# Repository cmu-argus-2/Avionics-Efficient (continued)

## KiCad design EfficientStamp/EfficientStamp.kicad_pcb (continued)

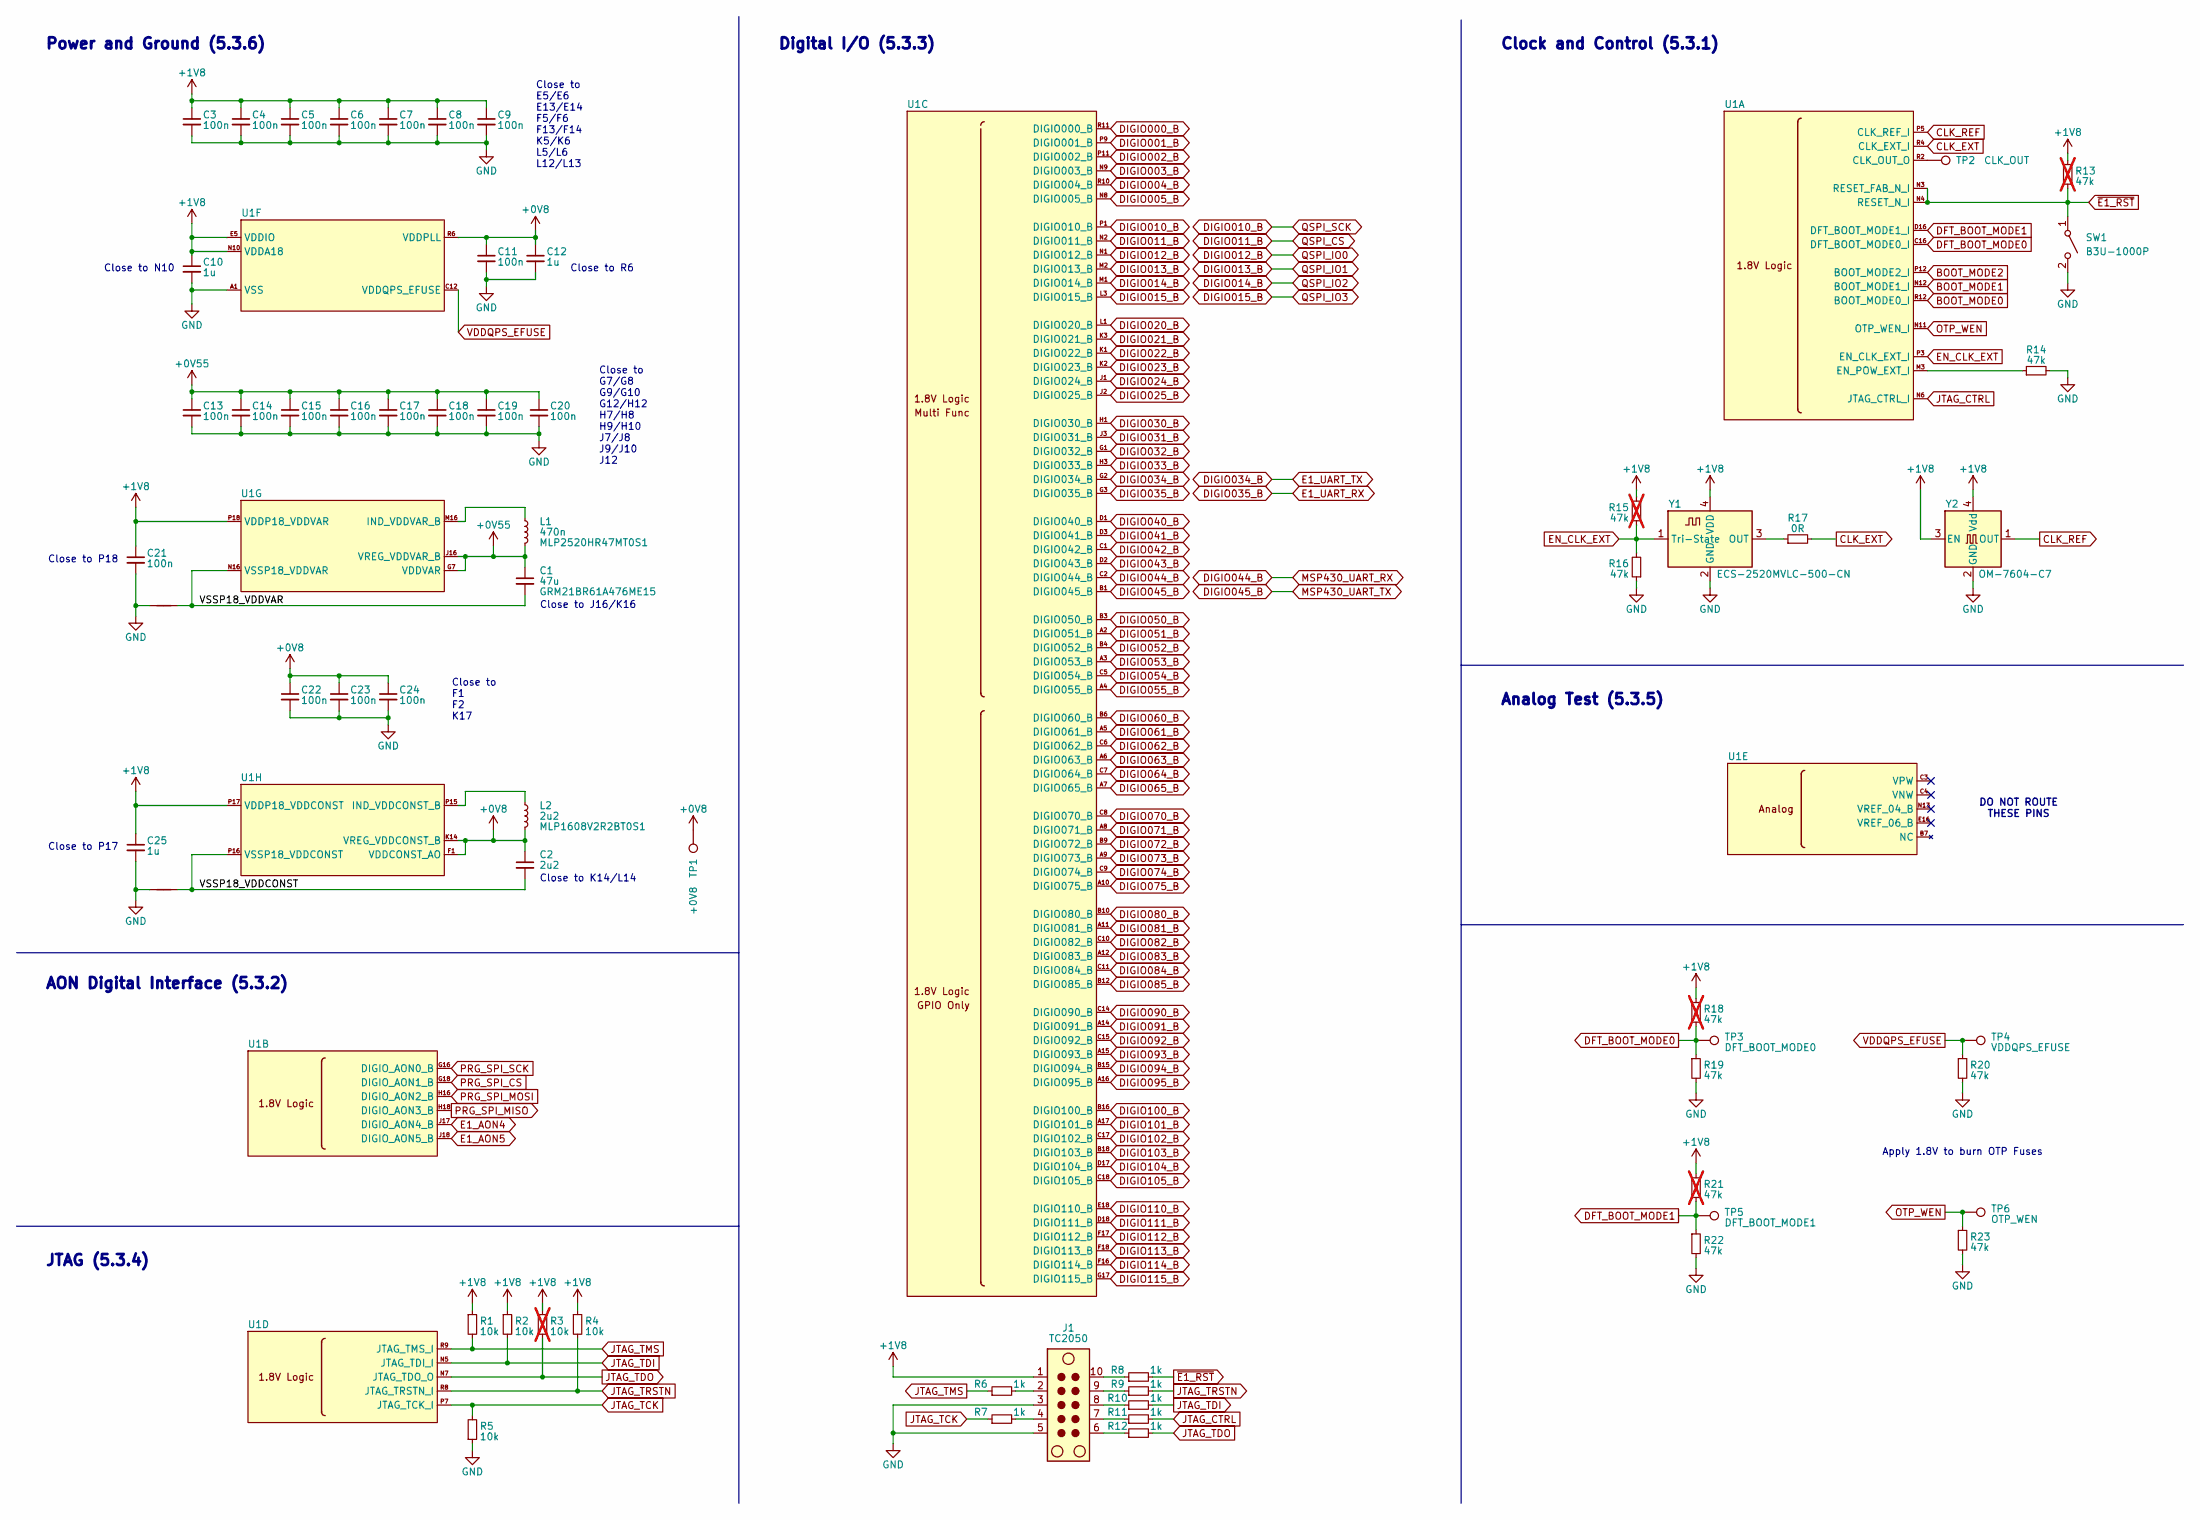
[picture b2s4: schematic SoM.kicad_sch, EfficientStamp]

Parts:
C1: 47u; C_0805_2012Metric; Part No. GRM21BR61A476ME15
C2: 2u2; C_0603_1608Metric
C3, C4, C5, C6, C7, C8, C9, C11, C13, C14, C15, C16, C17, C18, C19, C20, C21, C22, C23, C24: 100n; C_0201_0603Metric
C10, C12, C25: 1u; C_0402_1005Metric
J1: TC2050; Tag-Connect_TC2050-IDC-NL_2x05_P1.27mm_Vertical
L1: 470n; L_1008_2520Metric; Part No. MLP2520HR47MT0S1
L2: 2u2; L_0603_1608Metric; Part No. MLP1608V2R2BT0S1
NT1, NT2: NetTie_2; NetTie-2_SMD_Pad0.1mm
R1, R2, R4, R5: 10k; R_0402_1005Metric
R3: 10k; R_0402_1005Metric; not fitted
R6, R7, R8, R9, R10, R11, R12: 1k; R_0402_1005Metric
R13, R15, R18, R21: 47k; R_0402_1005Metric; not fitted
R14, R16, R19, R20, R22, R23: 47k; R_0402_1005Metric
R17: 0R; R_0402_1005Metric
SW1: B3U-1000P; SW_SPST_B3U-1000P
TP1: +0V8; TestPoint_Pad_D1.0mm
TP2: CLK_OUT; TestPoint_Pad_D1.0mm
TP3: DFT_BOOT_MODE0; TestPoint_Pad_D1.0mm
TP4: VDDQPS_EFUSE; TestPoint_Pad_D1.0mm
TP5: DFT_BOOT_MODE1; TestPoint_Pad_D1.0mm
TP6: OTP_WEN; TestPoint_Pad_D1.0mm
U1: Efficient E1x; WB-BGA-219_8.3x7.1mm_Layout17x15_P0.45mm_Ball0.45mm_Pad0.32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
Y1: ECS-2520MVLC-500-CN; Oscillator_SMD_ECS_2520MV-xxx-xx-4Pin_2.5x2.0mm
Y2: OM-7604-C7; OSC_OM-7604-C7-32.768KHZ-20PPM-TA-QC

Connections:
+0V8: C2.1, C11.1, C12.1, C22.1, C23.1, C24.1, L2.2, TP1.1 (1_1), U1.F1 (VDDCONST_AO), U1.F2 (VDDCONST_AO), U1.F3 (VDDCONST_AO), U1.K14 (VREG_VDDCONST_B), U1.K17 (VDDCONST_AO), U1.K18 (VDDCONST_AO), U1.L14 (VREG_VDDCONST_B), U1.R6 (VDDPLL)
+0V55: C1.1, C13.1, C14.1, C15.1, C16.1, C17.1, C18.1, C19.1, C20.1, L1.2, U1.G7 (VDDVAR), U1.G8 (VDDVAR), U1.G9 (VDDVAR), U1.G10 (VDDVAR), U1.G12 (VDDVAR), U1.H7 (VDDVAR), U1.H8 (VDDVAR), U1.H9 (VDDVAR), U1.H10 (VDDVAR), U1.H12 (VDDVAR), U1.J7 (VDDVAR), U1.J8 (VDDVAR), U1.J9 (VDDVAR), U1.J10 (VDDVAR), U1.J12 (VDDVAR), U1.J16 (VREG_VDDVAR_B), U1.K16 (VREG_VDDVAR_B); also elsewhere on the board
+1V8: C3.1, C4.1, C5.1, C6.1, C7.1, C8.1, C9.1, C10.1, C21.1, C25.1, J1.1, R1.1, R2.1, R3.1, R4.1, R13.2, R15.2, R18.1, R21.1, U1.E5 (VDDIO), U1.E6 (VDDIO), U1.E13 (VDDIO), U1.E14 (VDDIO), U1.F5 (VDDIO), U1.F6 (VDDIO), U1.F13 (VDDIO), U1.F14 (VDDIO), U1.K5 (VDDIO), U1.K6 (VDDIO), U1.L5 (VDDIO), U1.L6 (VDDIO), U1.L12 (VDDIO), U1.L13 (VDDIO), U1.N10 (VDDA18), U1.P17 (VDDP18_VDDCONST), U1.P18 (VDDP18_VDDVAR), U1.R17 (VDDP18_VDDCONST), U1.R18 (VDDP18_VDDVAR), Y1.4 (VDD), Y2.3 (EN), Y2.4 (Vdd); also elsewhere on the board
BOOT_MODE0: U1.R12 (BOOT_MODE0_I); also elsewhere on the board
BOOT_MODE1: U1.N12 (BOOT_MODE1_I); also elsewhere on the board
BOOT_MODE2: U1.P12 (BOOT_MODE2_I); also elsewhere on the board
CLK_EXT: R17.2, U1.R4 (CLK_EXT_I)
CLK_REF: U1.P5 (CLK_REF_I), Y2.1 (OUT)
DFT_BOOT_MODE0: R18.2, R19.1, TP3.1 (1_1), U1.C16 (DFT_BOOT_MODE0_I)
DFT_BOOT_MODE1: R21.2, R22.1, TP5.1 (1_1), U1.D16 (DFT_BOOT_MODE1_I)
DIGIO000_B: U1.R11 (DIGIO000_B); also elsewhere on the board
DIGIO001_B: U1.P9 (DIGIO001_B); also elsewhere on the board
DIGIO002_B: U1.P11 (DIGIO002_B); also elsewhere on the board
DIGIO003_B: U1.N9 (DIGIO003_B); also elsewhere on the board
DIGIO004_B: U1.R10 (DIGIO004_B); also elsewhere on the board
DIGIO005_B: U1.N8 (DIGIO005_B); also elsewhere on the board
DIGIO010_B: U1.P1 (DIGIO010_B); also elsewhere on the board
DIGIO011_B: U1.N2 (DIGIO011_B); also elsewhere on the board
DIGIO012_B: U1.N1 (DIGIO012_B); also elsewhere on the board
DIGIO013_B: U1.M2 (DIGIO013_B); also elsewhere on the board
DIGIO014_B: U1.M1 (DIGIO014_B); also elsewhere on the board
DIGIO015_B: U1.L3 (DIGIO015_B); also elsewhere on the board
DIGIO020_B: U1.L1 (DIGIO020_B); also elsewhere on the board
DIGIO021_B: U1.K3 (DIGIO021_B); also elsewhere on the board
DIGIO022_B: U1.K1 (DIGIO022_B); also elsewhere on the board
DIGIO023_B: U1.K2 (DIGIO023_B); also elsewhere on the board
DIGIO024_B: U1.J1 (DIGIO024_B); also elsewhere on the board
DIGIO025_B: U1.J2 (DIGIO025_B); also elsewhere on the board
DIGIO030_B: U1.H1 (DIGIO030_B); also elsewhere on the board
DIGIO031_B: U1.J3 (DIGIO031_B); also elsewhere on the board
DIGIO032_B: U1.G1 (DIGIO032_B); also elsewhere on the board
DIGIO033_B: U1.H3 (DIGIO033_B); also elsewhere on the board
DIGIO034_B: U1.G2 (DIGIO034_B); also elsewhere on the board
DIGIO035_B: U1.G3 (DIGIO035_B); also elsewhere on the board
DIGIO040_B: U1.D1 (DIGIO040_B); also elsewhere on the board
DIGIO041_B: U1.D3 (DIGIO041_B); also elsewhere on the board
DIGIO042_B: U1.C1 (DIGIO042_B); also elsewhere on the board
DIGIO043_B: U1.D2 (DIGIO043_B); also elsewhere on the board
DIGIO044_B: U1.C2 (DIGIO044_B); also elsewhere on the board
DIGIO045_B: U1.B1 (DIGIO045_B); also elsewhere on the board
DIGIO050_B: U1.B3 (DIGIO050_B); also elsewhere on the board
DIGIO051_B: U1.A2 (DIGIO051_B); also elsewhere on the board
DIGIO052_B: U1.B4 (DIGIO052_B); also elsewhere on the board
DIGIO053_B: U1.A3 (DIGIO053_B); also elsewhere on the board
DIGIO054_B: U1.C5 (DIGIO054_B); also elsewhere on the board
DIGIO055_B: U1.A4 (DIGIO055_B); also elsewhere on the board
DIGIO060_B: U1.B6 (DIGIO060_B); also elsewhere on the board
DIGIO061_B: U1.A5 (DIGIO061_B); also elsewhere on the board
DIGIO062_B: U1.C6 (DIGIO062_B); also elsewhere on the board
DIGIO063_B: U1.A6 (DIGIO063_B); also elsewhere on the board
DIGIO064_B: U1.C7 (DIGIO064_B); also elsewhere on the board
DIGIO065_B: U1.A7 (DIGIO065_B); also elsewhere on the board
DIGIO070_B: U1.C8 (DIGIO070_B); also elsewhere on the board
DIGIO071_B: U1.A8 (DIGIO071_B); also elsewhere on the board
DIGIO072_B: U1.B9 (DIGIO072_B); also elsewhere on the board
DIGIO073_B: U1.A9 (DIGIO073_B); also elsewhere on the board
DIGIO074_B: U1.C9 (DIGIO074_B); also elsewhere on the board
DIGIO075_B: U1.A10 (DIGIO075_B); also elsewhere on the board
DIGIO080_B: U1.B10 (DIGIO080_B); also elsewhere on the board
DIGIO081_B: U1.A11 (DIGIO081_B); also elsewhere on the board
DIGIO082_B: U1.C10 (DIGIO082_B); also elsewhere on the board
DIGIO083_B: U1.A12 (DIGIO083_B); also elsewhere on the board
DIGIO084_B: U1.C11 (DIGIO084_B); also elsewhere on the board
DIGIO085_B: U1.B12 (DIGIO085_B); also elsewhere on the board
DIGIO090_B: U1.C14 (DIGIO090_B); also elsewhere on the board
DIGIO091_B: U1.A14 (DIGIO091_B); also elsewhere on the board
DIGIO092_B: U1.C15 (DIGIO092_B); also elsewhere on the board
DIGIO093_B: U1.A15 (DIGIO093_B); also elsewhere on the board
DIGIO094_B: U1.B15 (DIGIO094_B); also elsewhere on the board
DIGIO095_B: U1.A16 (DIGIO095_B); also elsewhere on the board
DIGIO100_B: U1.B16 (DIGIO100_B); also elsewhere on the board
DIGIO101_B: U1.A17 (DIGIO101_B); also elsewhere on the board
DIGIO102_B: U1.C17 (DIGIO102_B); also elsewhere on the board
DIGIO103_B: U1.B18 (DIGIO103_B); also elsewhere on the board
DIGIO104_B: U1.D17 (DIGIO104_B); also elsewhere on the board
DIGIO105_B: U1.C18 (DIGIO105_B); also elsewhere on the board
DIGIO110_B: U1.E18 (DIGIO110_B); also elsewhere on the board
DIGIO111_B: U1.D18 (DIGIO111_B); also elsewhere on the board
DIGIO112_B: U1.F17 (DIGIO112_B); also elsewhere on the board
DIGIO113_B: U1.F18 (DIGIO113_B); also elsewhere on the board
DIGIO114_B: U1.F16 (DIGIO114_B); also elsewhere on the board
DIGIO115_B: U1.G17 (DIGIO115_B); also elsewhere on the board
E1_AON4: U1.J17 (DIGIO_AON4_B); also elsewhere on the board
E1_AON5: U1.J18 (DIGIO_AON5_B); also elsewhere on the board
EN_CLK_EXT: R15.1, R16.2, U1.P3 (EN_CLK_EXT_I), Y1.1 (Tri-State)
GND: C3.2, C4.2, C5.2, C6.2, C7.2, C8.2, C9.2, C10.2, C11.2, C12.2, C13.2, C14.2, C15.2, C16.2, C17.2, C18.2, C19.2, C20.2, C21.2, C22.2, C23.2, C24.2, C25.2, J1.3, J1.5, NT1.1, NT2.1, R5.1, R14.2, R16.1, R19.2, R20.2, R22.2, R23.2, SW1.2 (B), U1.A1 (VSS), U1.A18 (VSS), U1.B2 (VSS), U1.B5 (VSS), U1.B8 (VSS), U1.B11 (VSS), U1.B14 (VSS), U1.B17 (VSS), U1.E1 (VSS), U1.E2 (VSS), U1.E3 (VSS), U1.E7 (VSS), U1.E8 (VSS), U1.E9 (VSS), U1.E10 (VSS), U1.E12 (VSS), U1.E17 (VSS), U1.F7 (VSS), U1.F8 (VSS), U1.F9 (VSS), U1.F10 (VSS), U1.F12 (VSS), U1.G5 (VSS), U1.G6 (VSS), U1.G13 (VSS), U1.G14 (VSS), U1.H2 (VSS), U1.H5 (VSS), U1.H6 (VSS), U1.H13 (VSS), U1.H14 (VSS), U1.H17 (VSS), U1.J5 (VSS), U1.J6 (VSS), U1.J13 (VSS), U1.J14 (VSS), U1.K7 (VSS), U1.K8 (VSS), U1.K9 (VSS), U1.K10 (VSS), U1.K12 (VSS), U1.K13 (VSS), U1.L2 (VSS), U1.L7 (VSS), U1.L8 (VSS), U1.L9 (VSS), U1.L10 (VSS), U1.L16 (VSS), U1.L17 (VSS), U1.L18 (VSS), U1.N15 (VSS), U1.P2 (VSS), U1.P4 (VSS), U1.P6 (VSS), U1.P8 (VSS), U1.P10 (VSS), U1.P13 (VSS), U1.R1 (VSS), U1.R3 (VSS), U1.R5 (VSS), U1.R7 (VSS), U1.R13 (VSS), Y1.2 (GND), Y2.2 (GND); also elsewhere on the board
JTAG_CTRL: R11.2, U1.N6 (JTAG_CTRL_I); also elsewhere on the board
JTAG_TCK: R5.2, R7.1, U1.P7 (JTAG_TCK_I); also elsewhere on the board
JTAG_TDI: R2.2, R10.2, U1.N5 (JTAG_TDI_I); also elsewhere on the board
JTAG_TDO: R3.2, R12.2, U1.N7 (JTAG_TDO_O); also elsewhere on the board
JTAG_TMS: R1.2, R6.1, U1.R9 (JTAG_TMS_I); also elsewhere on the board
JTAG_TRSTN: R4.2, R9.2, U1.R8 (JTAG_TRSTN_I); also elsewhere on the board
unnamed: J1.2, R6.2
unnamed: J1.4, R7.2
unnamed: J1.6, R12.1
unnamed: J1.7, R11.1
unnamed: J1.8, R10.1
unnamed: J1.9, R9.1
unnamed: J1.10, R8.1
unnamed: L1.1, U1.M16 (IND_VDDVAR_B), U1.M17 (IND_VDDVAR_B), U1.M18 (IND_VDDVAR_B)
unnamed: L2.1, U1.P15 (IND_VDDCONST_B), U1.R15 (IND_VDDCONST_B)
unnamed: TP2.1 (1_1), U1.R2 (CLK_OUT_O)
unnamed: R14.1, U1.M3 (EN_POW_EXT_I)
unnamed: R17.1, Y1.3 (OUT)
OTP_WEN: R23.1, TP6.1 (1_1), U1.N11 (OTP_WEN_I)
PRG_SPI_CS: U1.G18 (DIGIO_AON1_B); also elsewhere on the board
PRG_SPI_MISO: U1.H18 (DIGIO_AON3_B); also elsewhere on the board
PRG_SPI_MOSI: U1.H16 (DIGIO_AON2_B); also elsewhere on the board
PRG_SPI_SCK: U1.G16 (DIGIO_AON0_B); also elsewhere on the board
VDDQPS_EFUSE: R20.1, TP4.1 (1_1), U1.C12 (VDDQPS_EFUSE)
VSSP18_VDDCONST: C2.2, NT2.2, U1.P16 (VSSP18_VDDCONST), U1.R16 (VSSP18_VDDCONST)
VSSP18_VDDVAR: C1.2, NT1.2, U1.N16 (VSSP18_VDDVAR), U1.N17 (VSSP18_VDDVAR), U1.N18 (VSSP18_VDDVAR)
~E1_RST: R8.2, R13.1, SW1.1 (A), U1.N3 (RESET_FAB_N_I), U1.N4 (RESET_N_I); also elsewhere on the board

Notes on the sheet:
Close to J16/K16
Clock and Control (5.3.1)
Close to F1 F2 K17
Close to P18
Digital I/O (5.3.3)
Analog Test (5.3.5)
Close to N10
Apply 1.8V to burn OTP Fuses
Close to G7/G8 G9/G10 G12/H12 H7/H8 H9/H10 J7/J8 J9/J10 J12
JTAG (5.3.4)
Close to R6
Close to E5/E6 E13/E14 F5/F6 F13/F14 K5/K6 L5/L6 L12/L13
AON Digital Interface (5.3.2)
Close to P17
Close to K14/L14
Power and Ground (5.3.6)
DO NOT ROUTE THESE PINS

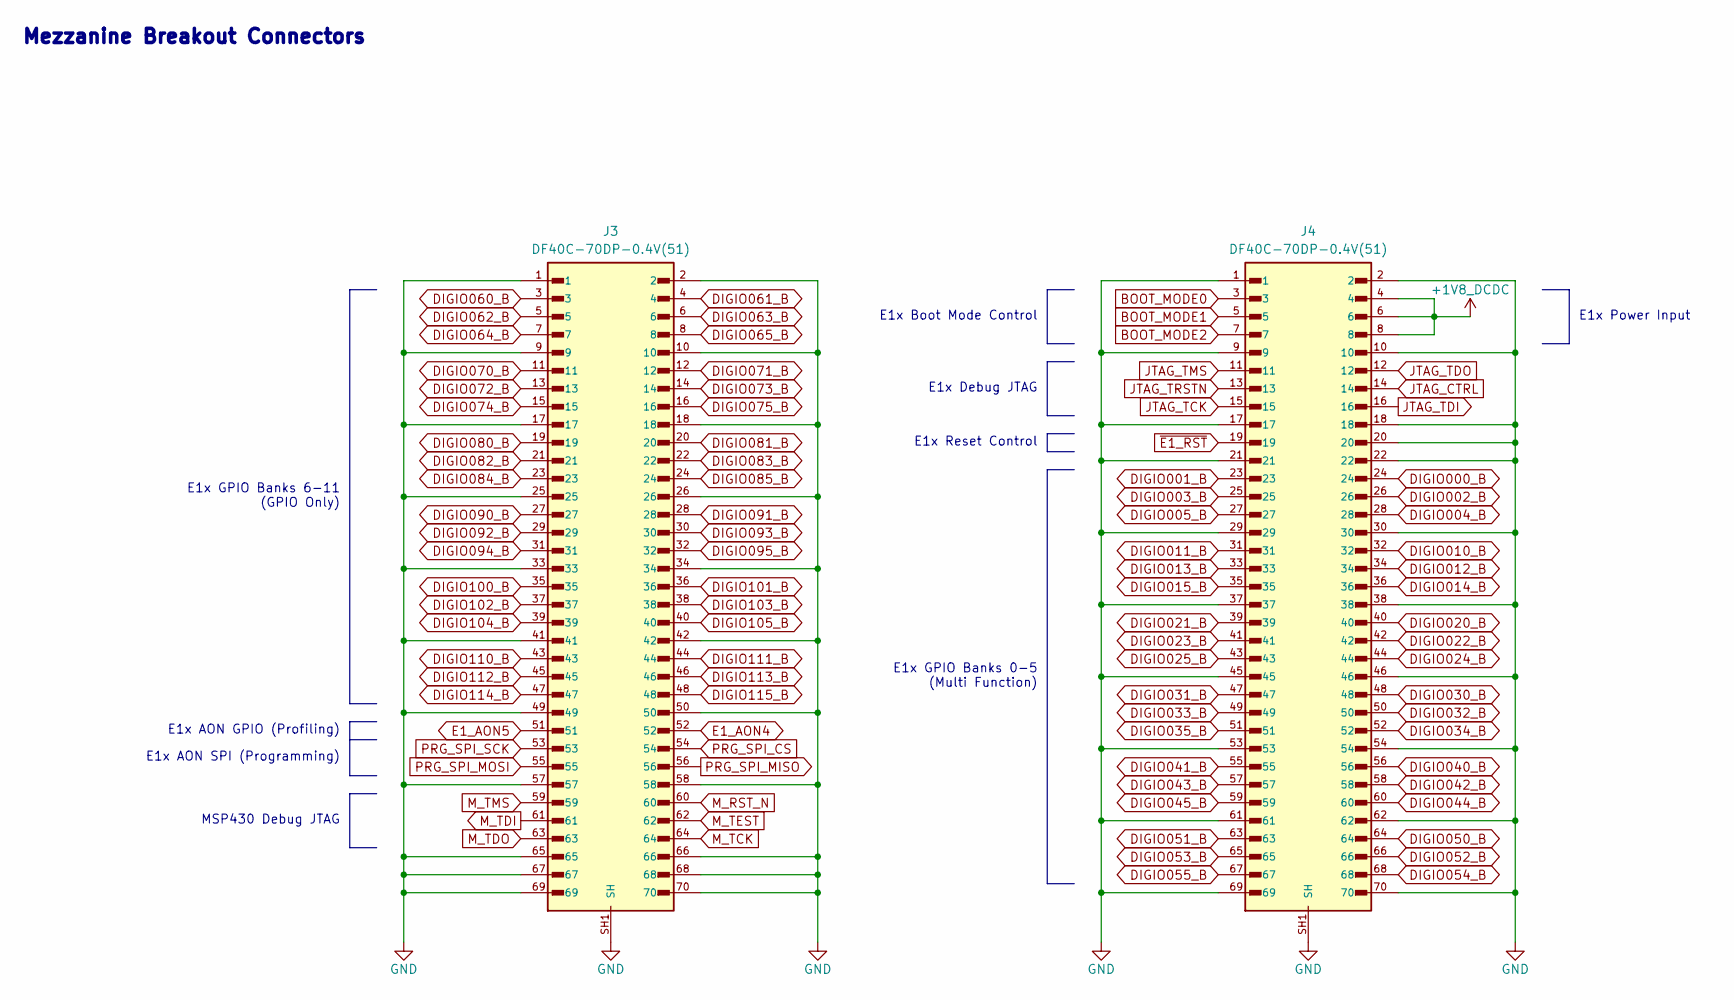
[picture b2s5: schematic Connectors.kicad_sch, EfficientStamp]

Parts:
J3, J4: DF40C-70DP-0.4V(51); HIROSE_DF40C-70DP-0.4V_51_

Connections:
+1V8_DCDC: J4.4, J4.6, J4.8; also elsewhere on the board
BOOT_MODE0: J4.3; also elsewhere on the board
BOOT_MODE1: J4.5; also elsewhere on the board
BOOT_MODE2: J4.7; also elsewhere on the board
DIGIO000_B: J4.24; also elsewhere on the board
DIGIO001_B: J4.23; also elsewhere on the board
DIGIO002_B: J4.26; also elsewhere on the board
DIGIO003_B: J4.25; also elsewhere on the board
DIGIO004_B: J4.28; also elsewhere on the board
DIGIO005_B: J4.27; also elsewhere on the board
DIGIO010_B: J4.32; also elsewhere on the board
DIGIO011_B: J4.31; also elsewhere on the board
DIGIO012_B: J4.34; also elsewhere on the board
DIGIO013_B: J4.33; also elsewhere on the board
DIGIO014_B: J4.36; also elsewhere on the board
DIGIO015_B: J4.35; also elsewhere on the board
DIGIO020_B: J4.40; also elsewhere on the board
DIGIO021_B: J4.39; also elsewhere on the board
DIGIO022_B: J4.42; also elsewhere on the board
DIGIO023_B: J4.41; also elsewhere on the board
DIGIO024_B: J4.44; also elsewhere on the board
DIGIO025_B: J4.43; also elsewhere on the board
DIGIO030_B: J4.48; also elsewhere on the board
DIGIO031_B: J4.47; also elsewhere on the board
DIGIO032_B: J4.50; also elsewhere on the board
DIGIO033_B: J4.49; also elsewhere on the board
DIGIO034_B: J4.52; also elsewhere on the board
DIGIO035_B: J4.51; also elsewhere on the board
DIGIO040_B: J4.56; also elsewhere on the board
DIGIO041_B: J4.55; also elsewhere on the board
DIGIO042_B: J4.58; also elsewhere on the board
DIGIO043_B: J4.57; also elsewhere on the board
DIGIO044_B: J4.60; also elsewhere on the board
DIGIO045_B: J4.59; also elsewhere on the board
DIGIO050_B: J4.64; also elsewhere on the board
DIGIO051_B: J4.63; also elsewhere on the board
DIGIO052_B: J4.66; also elsewhere on the board
DIGIO053_B: J4.65; also elsewhere on the board
DIGIO054_B: J4.68; also elsewhere on the board
DIGIO055_B: J4.67; also elsewhere on the board
DIGIO060_B: J3.3; also elsewhere on the board
DIGIO061_B: J3.4; also elsewhere on the board
DIGIO062_B: J3.5; also elsewhere on the board
DIGIO063_B: J3.6; also elsewhere on the board
DIGIO064_B: J3.7; also elsewhere on the board
DIGIO065_B: J3.8; also elsewhere on the board
DIGIO070_B: J3.11; also elsewhere on the board
DIGIO071_B: J3.12; also elsewhere on the board
DIGIO072_B: J3.13; also elsewhere on the board
DIGIO073_B: J3.14; also elsewhere on the board
DIGIO074_B: J3.15; also elsewhere on the board
DIGIO075_B: J3.16; also elsewhere on the board
DIGIO080_B: J3.19; also elsewhere on the board
DIGIO081_B: J3.20; also elsewhere on the board
DIGIO082_B: J3.21; also elsewhere on the board
DIGIO083_B: J3.22; also elsewhere on the board
DIGIO084_B: J3.23; also elsewhere on the board
DIGIO085_B: J3.24; also elsewhere on the board
DIGIO090_B: J3.27; also elsewhere on the board
DIGIO091_B: J3.28; also elsewhere on the board
DIGIO092_B: J3.29; also elsewhere on the board
DIGIO093_B: J3.30; also elsewhere on the board
DIGIO094_B: J3.31; also elsewhere on the board
DIGIO095_B: J3.32; also elsewhere on the board
DIGIO100_B: J3.35; also elsewhere on the board
DIGIO101_B: J3.36; also elsewhere on the board
DIGIO102_B: J3.37; also elsewhere on the board
DIGIO103_B: J3.38; also elsewhere on the board
DIGIO104_B: J3.39; also elsewhere on the board
DIGIO105_B: J3.40; also elsewhere on the board
DIGIO110_B: J3.43; also elsewhere on the board
DIGIO111_B: J3.44; also elsewhere on the board
DIGIO112_B: J3.45; also elsewhere on the board
DIGIO113_B: J3.46; also elsewhere on the board
DIGIO114_B: J3.47; also elsewhere on the board
DIGIO115_B: J3.48; also elsewhere on the board
E1_AON4: J3.52; also elsewhere on the board
E1_AON5: J3.51; also elsewhere on the board
GND: J3.1, J3.2, J3.9, J3.10, J3.17, J3.18, J3.25, J3.26, J3.33, J3.34, J3.41, J3.42, J3.49, J3.50, J3.57, J3.58, J3.65, J3.66, J3.67, J3.68, J3.69, J3.70, J3.SH1 (SH), J3.SH2 (SH), J3.SH3 (SH), J3.SH4 (SH), J4.1, J4.2, J4.9, J4.10, J4.17, J4.18, J4.20, J4.21, J4.22, J4.29, J4.30, J4.37, J4.38, J4.45, J4.46, J4.53, J4.54, J4.61, J4.62, J4.69, J4.70, J4.SH1 (SH), J4.SH2 (SH), J4.SH3 (SH), J4.SH4 (SH); also elsewhere on the board
JTAG_CTRL: J4.14; also elsewhere on the board
JTAG_TCK: J4.15; also elsewhere on the board
JTAG_TDI: J4.16; also elsewhere on the board
JTAG_TDO: J4.12; also elsewhere on the board
JTAG_TMS: J4.11; also elsewhere on the board
JTAG_TRSTN: J4.13; also elsewhere on the board
M_RST_N: J3.60; also elsewhere on the board
M_TCK: J3.64; also elsewhere on the board
M_TDI: J3.61; also elsewhere on the board
M_TDO: J3.63; also elsewhere on the board
M_TEST: J3.62; also elsewhere on the board
M_TMS: J3.59; also elsewhere on the board
PRG_SPI_CS: J3.54; also elsewhere on the board
PRG_SPI_MISO: J3.56; also elsewhere on the board
PRG_SPI_MOSI: J3.55; also elsewhere on the board
PRG_SPI_SCK: J3.53; also elsewhere on the board
~E1_RST: J4.19; also elsewhere on the board

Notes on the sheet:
MSP430 Debug JTAG
E1x AON SPI (Programming)
Mezzanine Breakout Connectors
E1x Reset Control
E1x AON GPIO (Profiling)
E1x Power Input
E1x Debug JTAG
E1x Boot Mode Control
E1x GPIO Banks 0-5 (Multi Function)
E1x GPIO Banks 6-11 (GPIO Only)

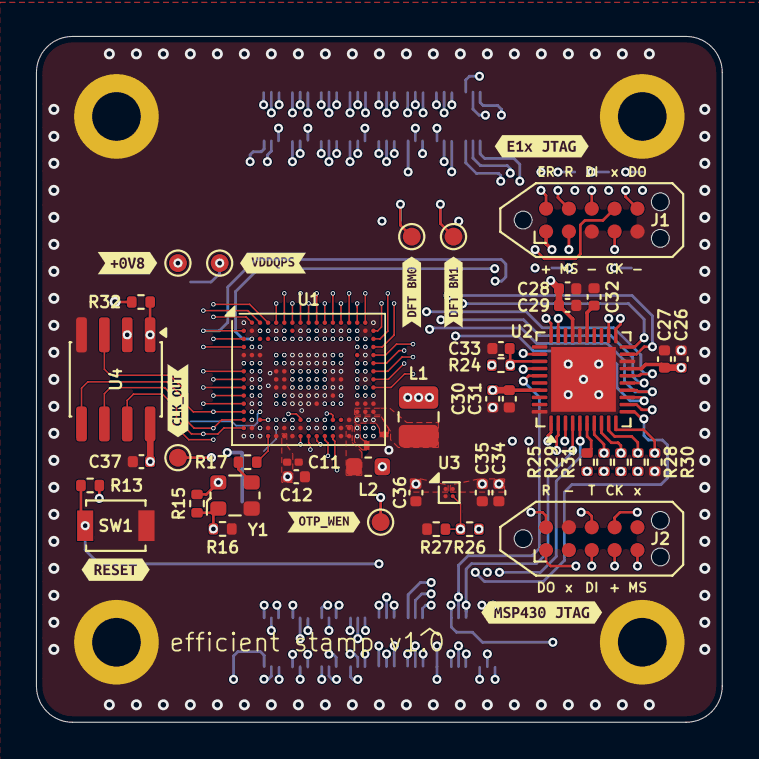
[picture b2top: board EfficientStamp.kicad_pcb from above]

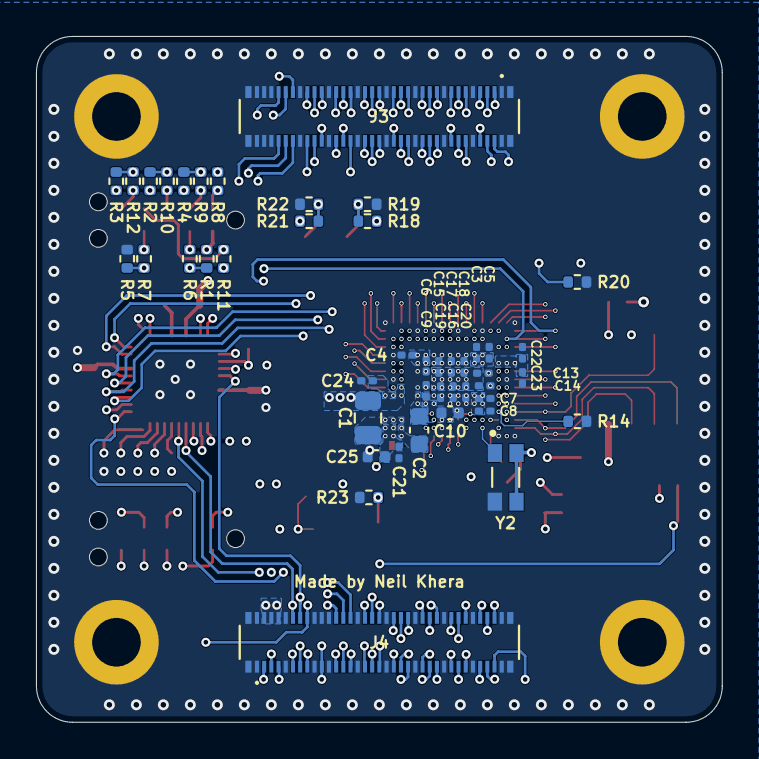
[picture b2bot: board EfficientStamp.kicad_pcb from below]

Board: 6 copper layers, 38.1 x 38.1 mm, 103 parts (45 on the bottom side), 123 nets.

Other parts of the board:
kibuzzard-6A01F62C: G***; kibuzzard-6A01F62C
kibuzzard-69F3B4A5: G***; kibuzzard-69F3B4A5
kibuzzard-69F3B25A: G***; kibuzzard-69F3B25A
kibuzzard-69F3B40E: G***; kibuzzard-69F3B40E
kibuzzard-69F3B165: G***; kibuzzard-69F3B165
kibuzzard-69F3B219: G***; kibuzzard-69F3B219
kibuzzard-69F3B242: G***; kibuzzard-69F3B242
kibuzzard-69F3B417: G***; kibuzzard-69F3B417
kibuzzard-69F3B503: G***; kibuzzard-69F3B503

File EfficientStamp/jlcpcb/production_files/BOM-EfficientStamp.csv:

Comment,Designator,Footprint,LCSC,Quantity
0R,"R17,R25",R_0402_1005Metric,C5374047,2
100n,"C11,C13,C14,C15,C16,C17,C18,C19,C20,C21,C22,C23,C24,C3,C4,C5,C6,C7,C8,C9",C_0201_0603Metric,C76934,20
100n,"C27,C29,C31",C_0402_1005Metric,C77014,3
10k,"R1,R2,R28,R30,R31,R32,R4,R5",R_0402_1005Metric,C2484841,8
10u,"C26,C28,C30,C34,C36",C_0402_1005Metric,C408132,5
1k,"R10,R11,R12,R6,R7,R8,R9",R_0402_1005Metric,C2479070,7
1u,"C10,C12,C25,C35,C37",C_0402_1005Metric,C76999,5
2n2,C33,C_0402_1005Metric,C77022,1
2u2,L2,L_0603_1608Metric,C383367,1
2u2,C2,C_0603_1608Metric,C86018,1
470n,C32,C_0402_1005Metric,C88946,1
47k,"R14,R16,R19,R20,R22,R23,R24,R27",R_0402_1005Metric,C4266769,8
47u,C1,C_0805_2012Metric,C124129,1
B3U-1000P,SW1,SW_SPST_B3U-1000P,C231329,1
DF40C-70DP-0.4V(51),"J3,J4",HIROSE_DF40C-70DP-0.4V_51_,C2692097,2
ECS-2520MVLC-500-CN,Y1,Oscillator_SMD_ECS_2520MV-xxx-xx-4Pin_2.5x2.0mm,C17348430,1
IS25WJ032F-JNLE,U4,SOIC-8_3.9x4.9mm_P1.27mm,C7290366,1
OM-7604-C7,Y2,OSC_OM-7604-C7-32.768KHZ-20PPM-TA-QC,C5341289,1
TPS22916BYFPR,U3,Texas_PicoStar_BGA-4_0.758x0.758mm_Layout2x2_P0.4mm,C2150095,1
470n,L1,L_1008_2520Metric,,1
DFT_BOOT_MODE0,TP3,TestPoint_Pad_D1.0mm,,1
DFT_BOOT_MODE1,TP5,TestPoint_Pad_D1.0mm,,1
+0V8,TP1,TestPoint_Pad_D1.0mm,,1
VDDQPS_EFUSE,TP4,TestPoint_Pad_D1.0mm,,1
CLK_OUT,TP2,TestPoint_Pad_D1.0mm,,1
Efficient E1x,U1,WB-BGA-219_8.3x7.1mm_Layout17x15_P0.45mm_Ball0.45mm_Pad0.32mm_NSMD_Actual2,,1
MSP430F5151IRSBT,U2,VQFN-40-1EP_5x5mm_P0.4mm_EP3.6x3.6mm,,1
OTP_WEN,TP6,TestPoint_Pad_D1.0mm,,1

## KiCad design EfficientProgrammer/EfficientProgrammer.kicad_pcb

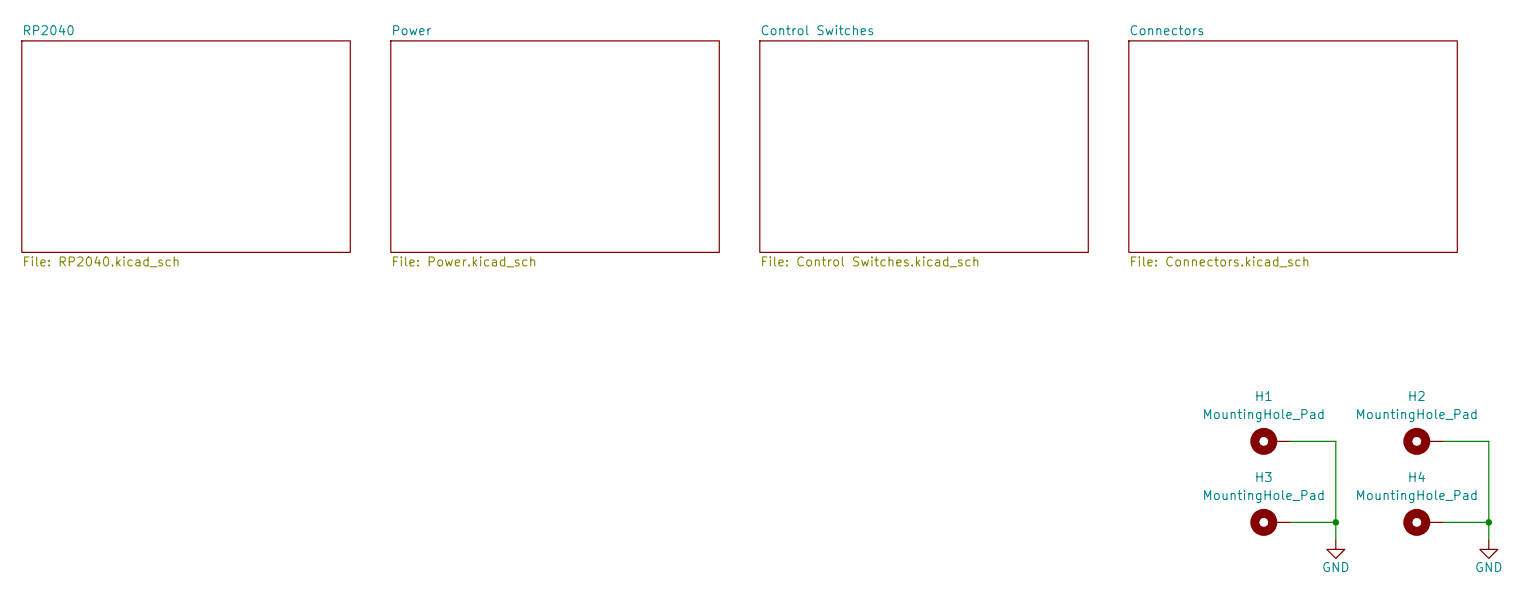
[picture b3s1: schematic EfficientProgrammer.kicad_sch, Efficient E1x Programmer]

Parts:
H1, H2, H3, H4: MountingHole_Pad; MountingHole_2.7mm_M2.5_DIN965_Pad

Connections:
GND: H1.1 (1_1), H2.1 (1_1), H3.1 (1_1), H4.1 (1_1); also elsewhere on the board

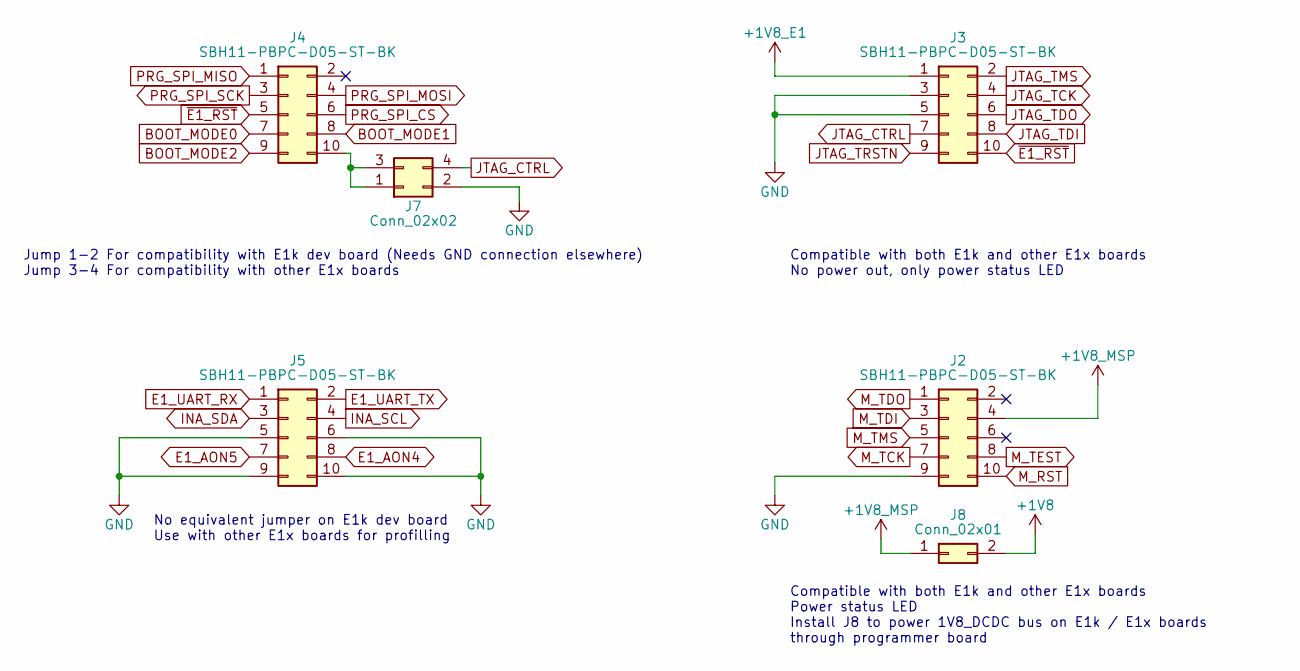
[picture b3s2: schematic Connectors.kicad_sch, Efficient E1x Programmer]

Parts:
J2, J3, J4, J5: SBH11-PBPC-D05-ST-BK; IDC-Header_2x05_P2.54mm_Vertical
J7: Conn_02x02; PinHeader_2x02_P2.54mm_Vertical
J8: Conn_02x01; PinHeader_2x01_P2.54mm_Vertical

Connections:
+1V8: J8.2; also elsewhere on the board
+1V8_E1: J3.1
+1V8_MSP: J2.4, J8.1
BOOT_MODE0: J4.7; also elsewhere on the board
BOOT_MODE1: J4.8; also elsewhere on the board
BOOT_MODE2: J4.9; also elsewhere on the board
E1_AON4: J5.8; also elsewhere on the board
E1_AON5: J5.7; also elsewhere on the board
E1_UART_RX: J5.1; also elsewhere on the board
E1_UART_TX: J5.2; also elsewhere on the board
GND: J2.9, J3.3, J3.5, J5.5, J5.6, J5.9, J5.10, J7.2; also elsewhere on the board
INA_SCL: J5.4; also elsewhere on the board
INA_SDA: J5.3; also elsewhere on the board
JTAG_CTRL: J3.7, J7.4; also elsewhere on the board
JTAG_TCK: J3.4; also elsewhere on the board
JTAG_TDI: J3.8; also elsewhere on the board
JTAG_TDO: J3.6; also elsewhere on the board
JTAG_TMS: J3.2; also elsewhere on the board
JTAG_TRSTN: J3.9; also elsewhere on the board
M_RST: J2.10; also elsewhere on the board
M_TCK: J2.7; also elsewhere on the board
M_TDI: J2.3; also elsewhere on the board
M_TDO: J2.1; also elsewhere on the board
M_TEST: J2.8; also elsewhere on the board
M_TMS: J2.5; also elsewhere on the board
unnamed: J4.10, J7.1, J7.3
PRG_SPI_CS: J4.6; also elsewhere on the board
PRG_SPI_MISO: J4.1; also elsewhere on the board
PRG_SPI_MOSI: J4.4; also elsewhere on the board
PRG_SPI_SCK: J4.3; also elsewhere on the board
~E1_RST: J3.10, J4.5; also elsewhere on the board

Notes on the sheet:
Compatible with both E1k and other E1x boards No power out, only power status LED
No equivalent jumper on E1k dev board Use with other E1x boards for profilling
Compatible with both E1k and other E1x boards Power status LED Install J8 to power 1V8_DCDC bus on E1k / E1x boards through programmer board
Jump 1-2 For compatibility with E1k dev board (Needs GND connection elsewhere) Jump 3-4 For compatibility with other E1x boards
